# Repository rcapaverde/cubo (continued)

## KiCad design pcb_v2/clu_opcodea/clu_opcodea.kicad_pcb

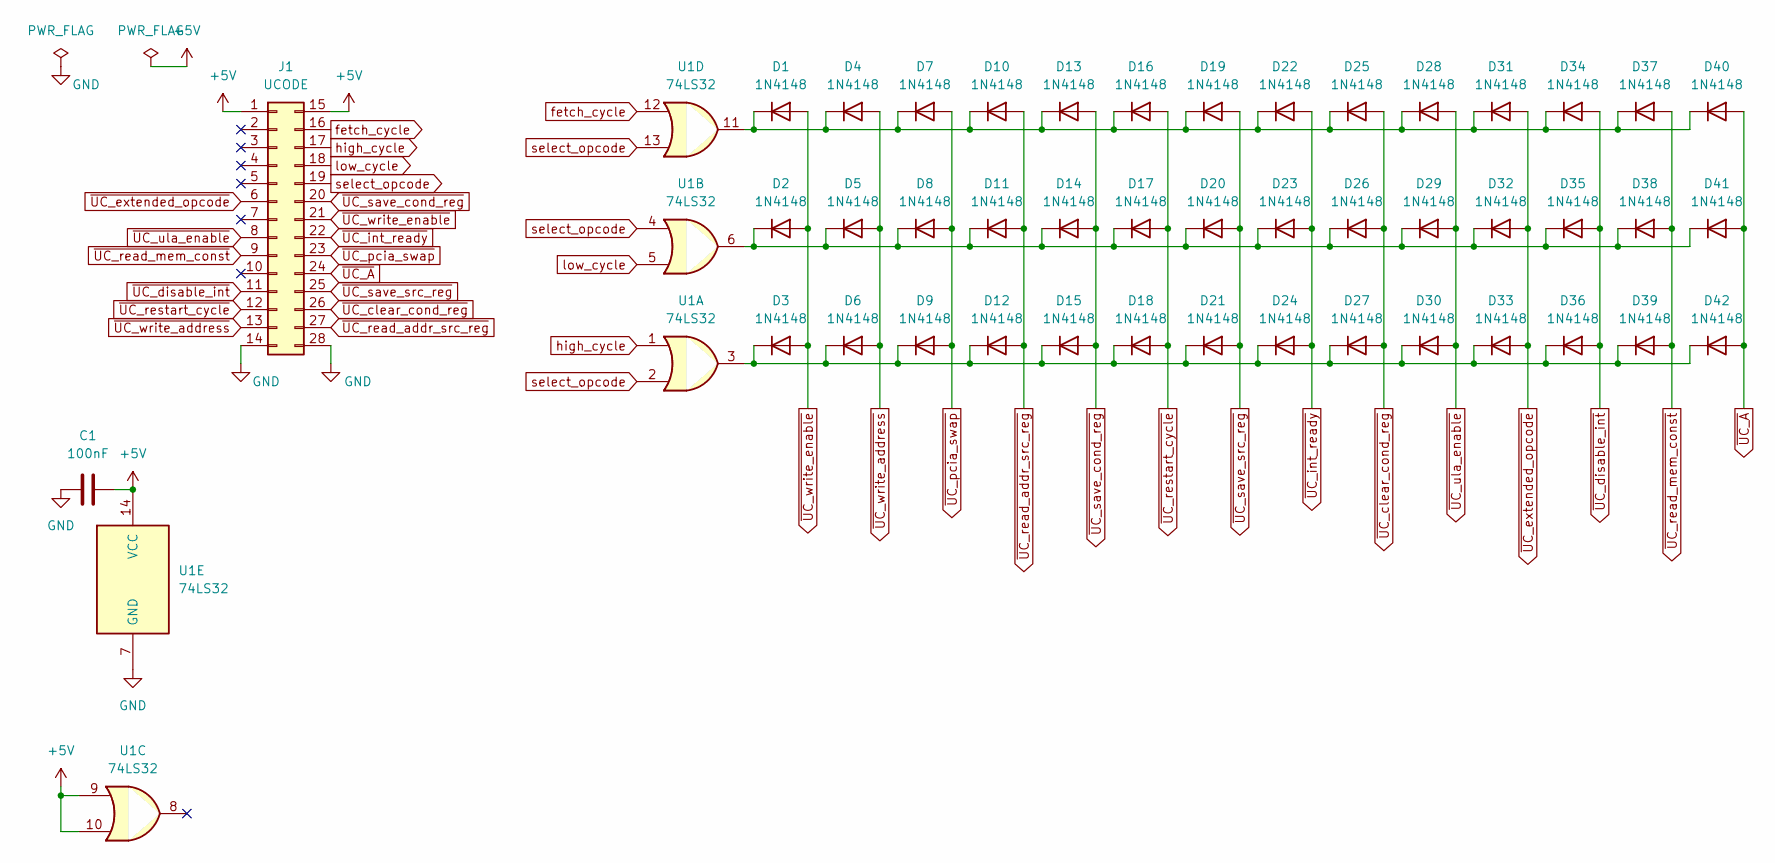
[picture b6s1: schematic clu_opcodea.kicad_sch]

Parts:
C1: 100nF; C_Disc_D5.1mm_W3.2mm_P5.00mm
D1, D2, D3, D4, D5, D6, D7, D8, D9, D10, D11, D12, D13, D14, D15, D16, D17, D18, D19, D20, D21, D22, D23, D24, D25, D26, D27, D28, D29, D30, D31, D32, D33, D34, D35, D36, D37, D38, D39, D40, D41, D42: 1N4148; D_DO-35_SOD27_P2.54mm_Vertical_AnodeUp
J1: UCODE; edge-conector-14
U1: 74LS32; DIP-14_W7.62mm

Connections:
+5V: C1.2, J1.1, J1.15, U1.9, U1.10, U1.14 (VCC)
GND: C1.1, J1.14, J1.28, U1.7 (GND)
unnamed: D1.1 (K), D4.1 (K), D7.1 (K), D10.1 (K), D13.1 (K), D16.1 (K), D19.1 (K), D22.1 (K), D25.1 (K), D28.1 (K), D31.1 (K), D34.1 (K), D37.1 (K), D40.1 (K), U1.11
unnamed: D2.1 (K), D5.1 (K), D8.1 (K), D11.1 (K), D14.1 (K), D17.1 (K), D20.1 (K), D23.1 (K), D26.1 (K), D29.1 (K), D32.1 (K), D35.1 (K), D38.1 (K), D41.1 (K), U1.6
unnamed: D3.1 (K), D6.1 (K), D9.1 (K), D12.1 (K), D15.1 (K), D18.1 (K), D21.1 (K), D24.1 (K), D27.1 (K), D30.1 (K), D33.1 (K), D36.1 (K), D39.1 (K), D42.1 (K), U1.3
fetch_cycle: J1.16, U1.12
high_cycle: J1.17, U1.1
low_cycle: J1.18, U1.5
select_opcode: J1.19, U1.2, U1.4, U1.13
~UC_A: D40.2 (A), D41.2 (A), D42.2 (A), J1.24
~UC_clear_cond_reg: D25.2 (A), D26.2 (A), D27.2 (A), J1.26
~UC_disable_int: D34.2 (A), D35.2 (A), D36.2 (A), J1.11
~UC_extended_opcode: D31.2 (A), D32.2 (A), D33.2 (A), J1.6
~UC_int_ready: D22.2 (A), D23.2 (A), D24.2 (A), J1.22
~UC_pcia_swap: D7.2 (A), D8.2 (A), D9.2 (A), J1.23
~UC_read_addr_src_reg: D10.2 (A), D11.2 (A), D12.2 (A), J1.27
~UC_read_mem_const: D37.2 (A), D38.2 (A), D39.2 (A), J1.9
~UC_restart_cycle: D16.2 (A), D17.2 (A), D18.2 (A), J1.12
~UC_save_cond_reg: D13.2 (A), D14.2 (A), D15.2 (A), J1.20
~UC_save_src_reg: D19.2 (A), D20.2 (A), D21.2 (A), J1.25
~UC_ula_enable: D28.2 (A), D29.2 (A), D30.2 (A), J1.8
~UC_write_address: D4.2 (A), D5.2 (A), D6.2 (A), J1.13
~UC_write_enable: D1.2 (A), D2.2 (A), D3.2 (A), J1.21

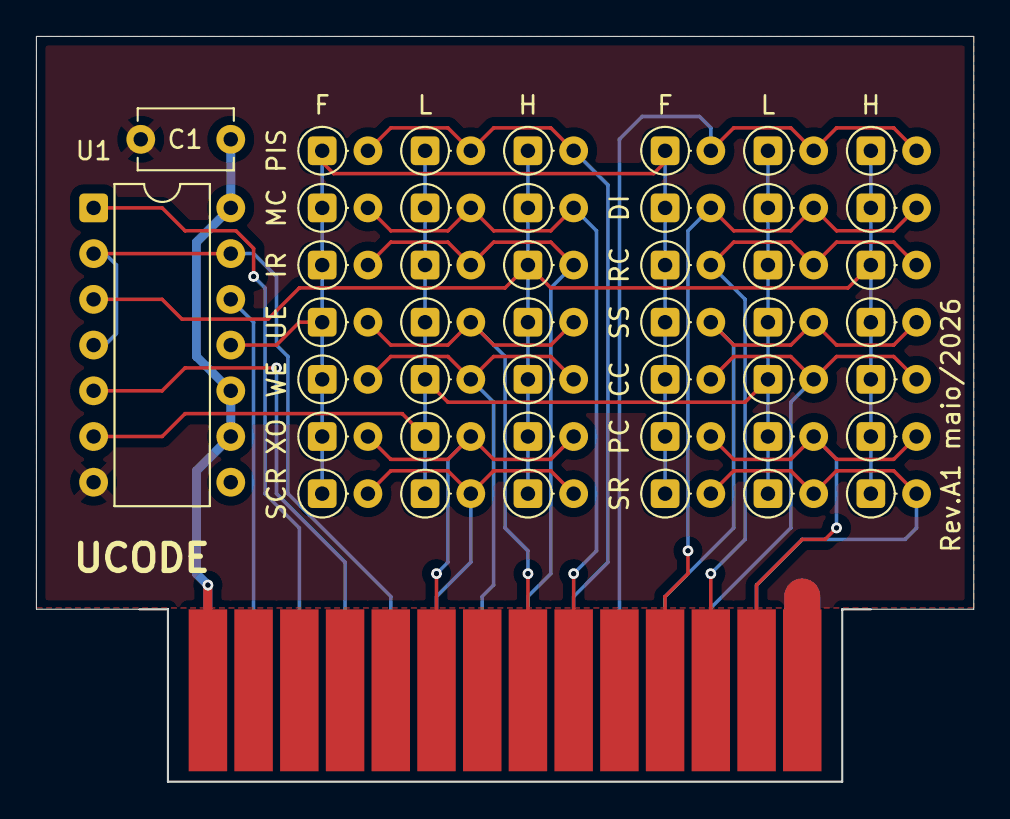
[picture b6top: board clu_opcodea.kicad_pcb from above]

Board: 2 copper layers, 52.1 x 41.4 mm, 45 parts (0 on the bottom side), 23 nets.

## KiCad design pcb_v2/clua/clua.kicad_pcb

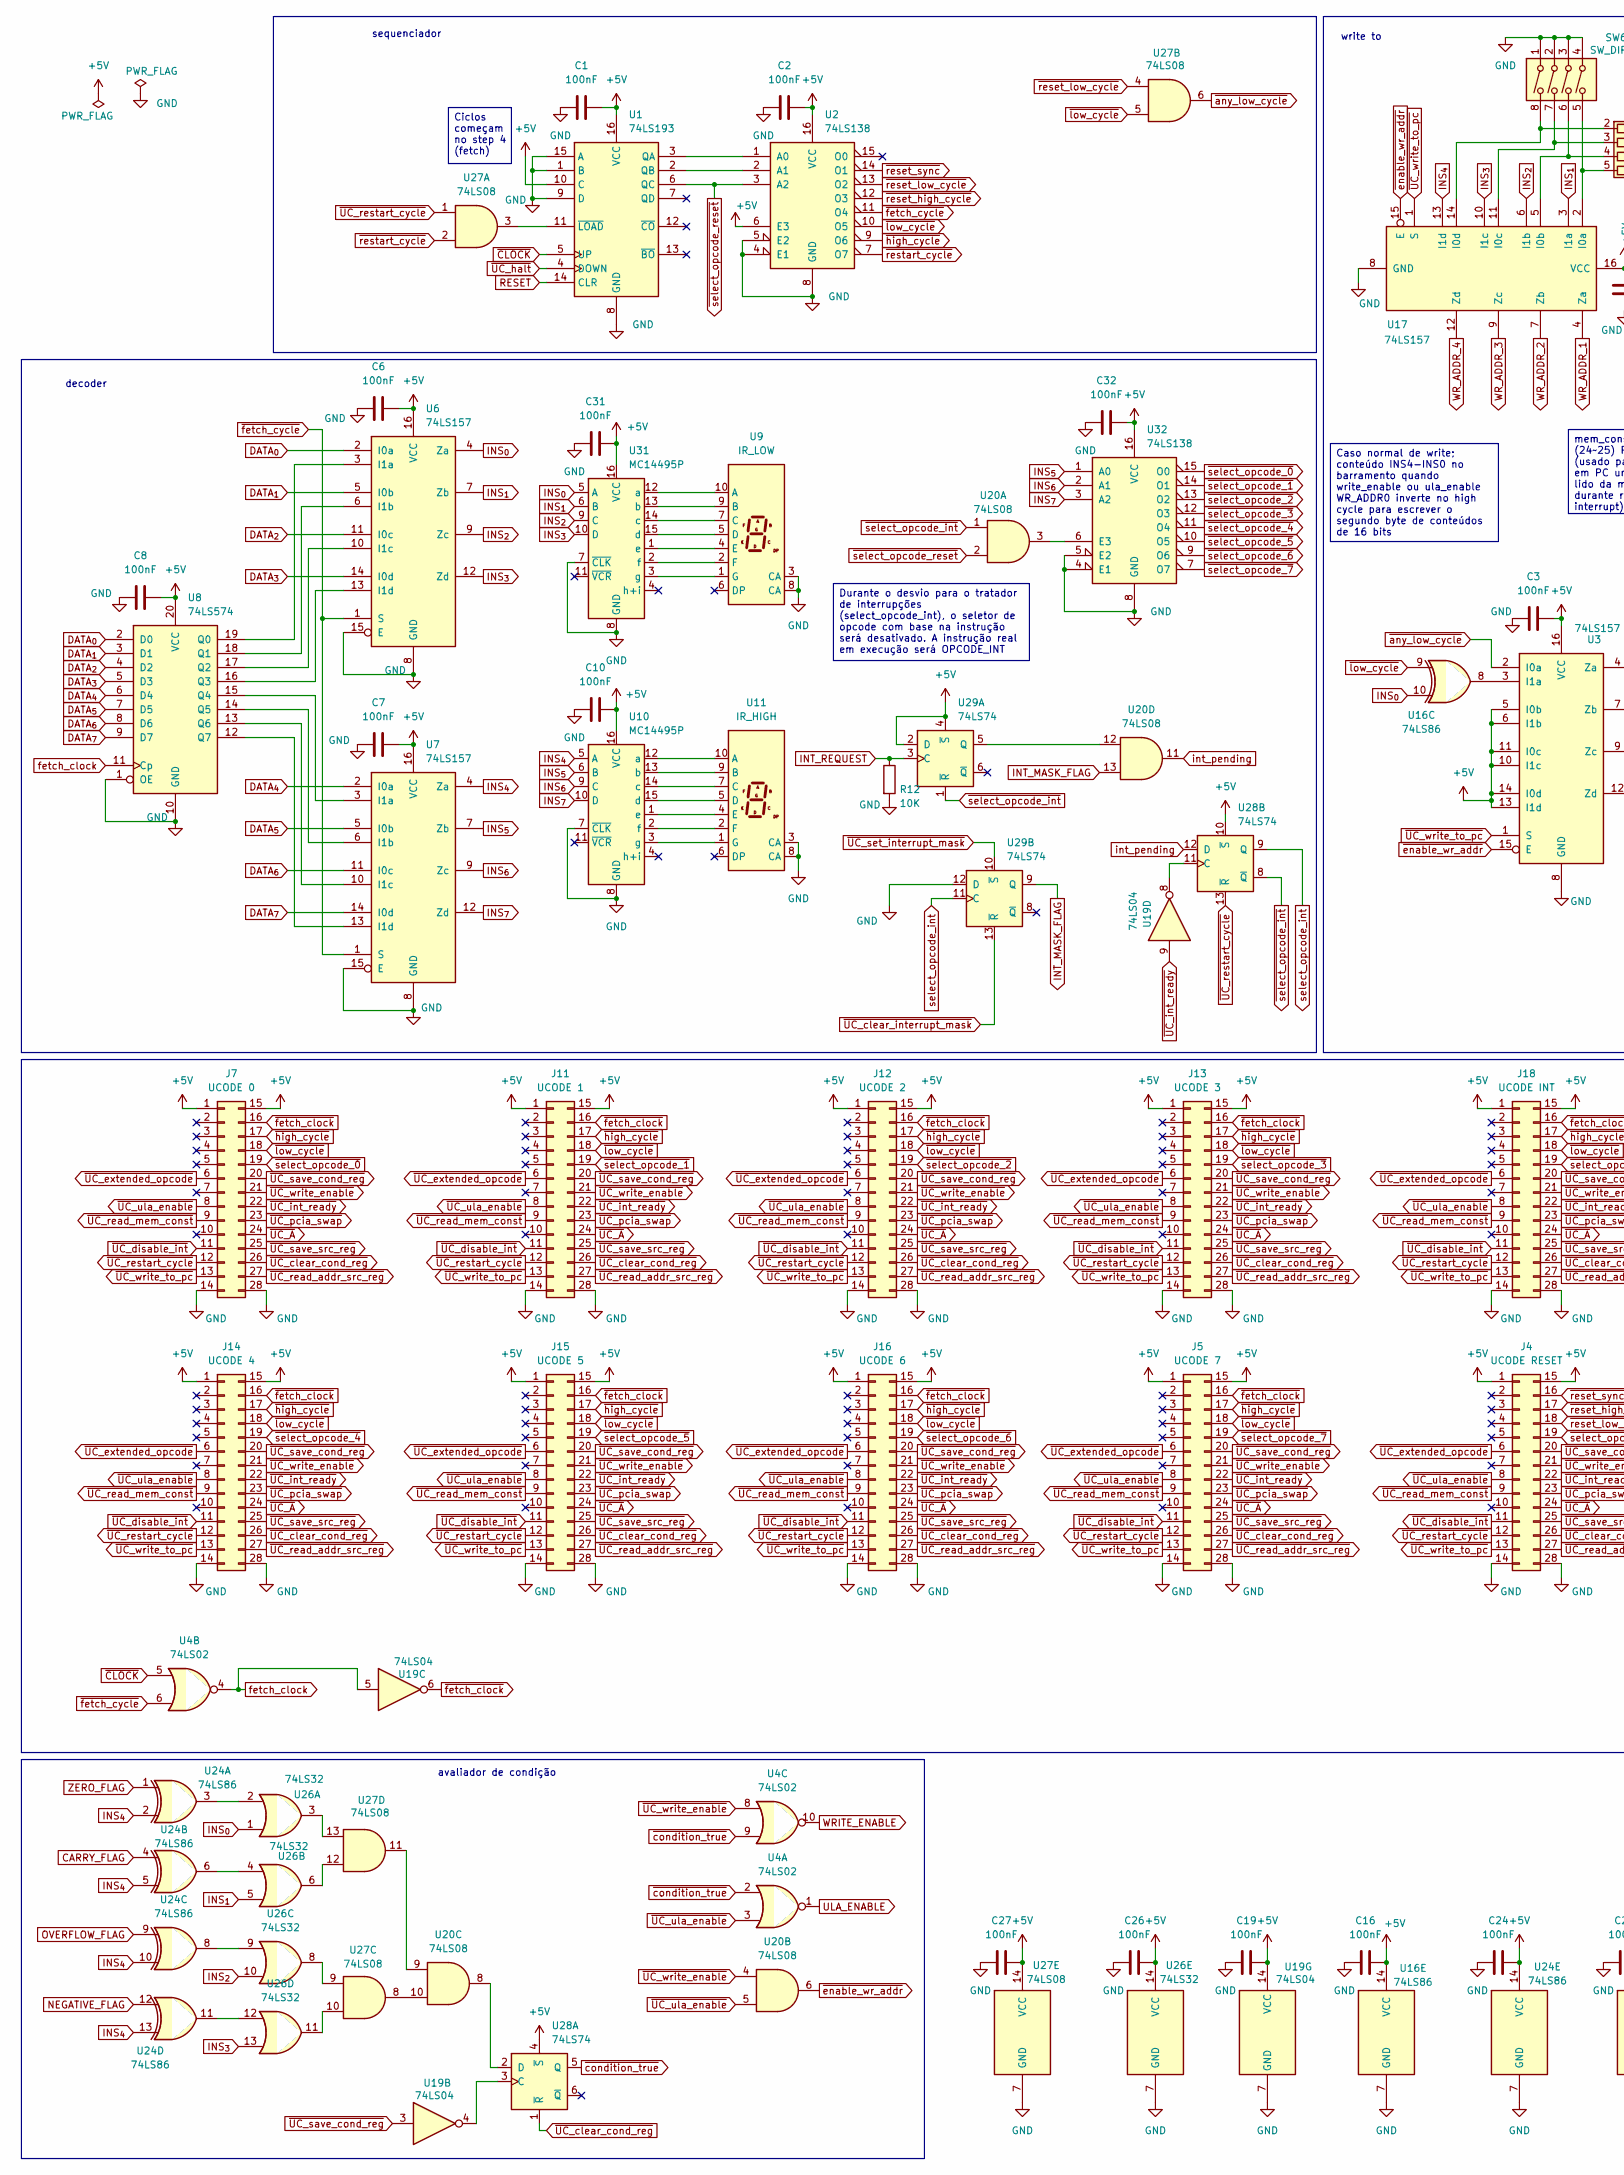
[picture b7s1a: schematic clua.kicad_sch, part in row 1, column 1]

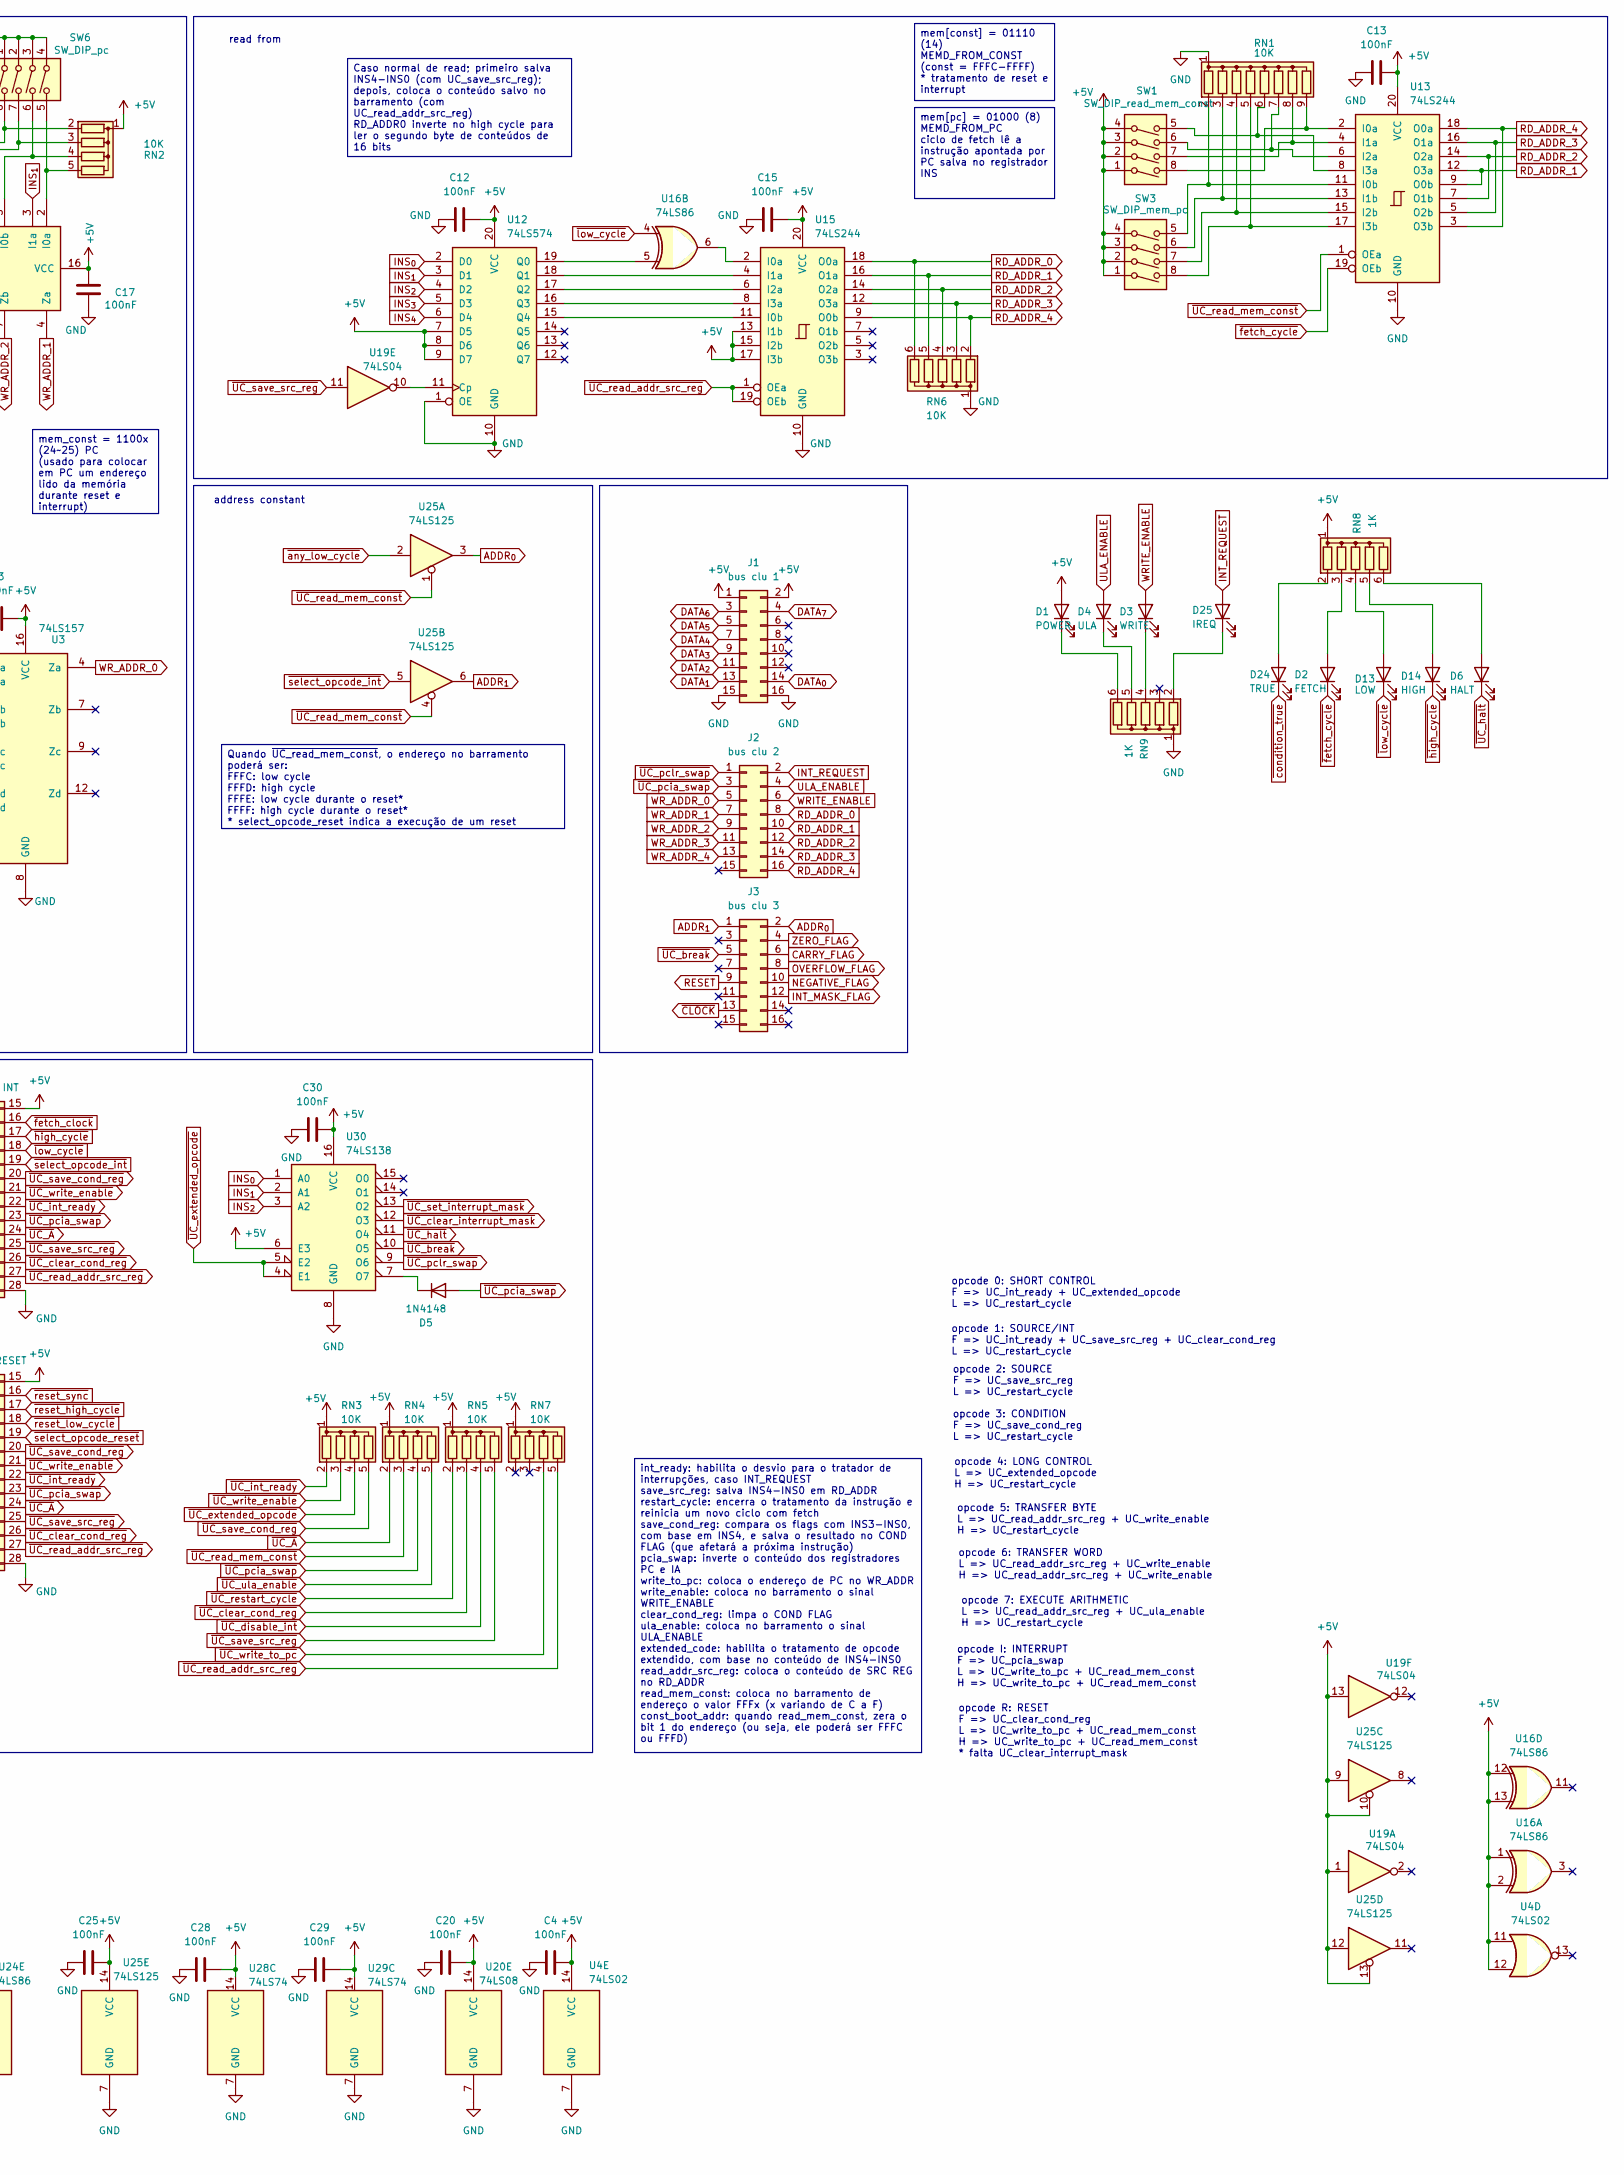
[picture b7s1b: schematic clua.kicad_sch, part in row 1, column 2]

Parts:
C1, C2, C3, C4, C6, C7, C8, C10, C12, C13, C15, C16, C17, C19, C20, C24, C25, C26, C27, C28, C29, C30, C31, C32: 100nF; C_Disc_D5.1mm_W3.2mm_P5.00mm
D1: POWER; LED_D5.0mm
D2: FETCH; LED_D5.0mm
D3: WRITE; LED_D5.0mm
D4: ULA; LED_D5.0mm
D5: 1N4148; D_DO-35_SOD27_P7.62mm_Horizontal
D6: HALT; LED_D5.0mm
D13: LOW; LED_D5.0mm
D14: HIGH; LED_D5.0mm
D24: TRUE; LED_D5.0mm
D25: IREQ; LED_D5.0mm
J1: bus clu 1; conector 02x08
J2: bus clu 2; conector 02x08
J3: bus clu 3; conector 02x08
J4: UCODE RESET; male-edge-connector-28
J5: UCODE 7; male-edge-connector-28
J7: UCODE 0; male-edge-connector-28
J11: UCODE 1; male-edge-connector-28
J12: UCODE 2; male-edge-connector-28
J13: UCODE 3; male-edge-connector-28
J14: UCODE 4; male-edge-connector-28
J15: UCODE 5; male-edge-connector-28
J16: UCODE 6; male-edge-connector-28
J18: UCODE INT; male-edge-connector-28
R12: 10K; R_Axial_DIN0207_L6.3mm_D2.5mm_P7.62mm_Horizontal
RN1: 10K; R_Array_SIP9
RN2, RN3, RN4, RN5, RN7: 10K; R_Array_SIP5
RN6: 10K; R_Array_SIP6
RN8, RN9: 1K; R_Array_SIP6
SW1: SW_DIP_read_mem_const; SW_DIP_SPSTx04_Slide_6.7x11.72mm_W7.62mm_P2.54mm_LowProfile
SW3: SW_DIP_mem_pc; SW_DIP_SPSTx04_Slide_6.7x11.72mm_W7.62mm_P2.54mm_LowProfile
SW6: SW_DIP_pc; SW_DIP_SPSTx04_Slide_6.7x11.72mm_W7.62mm_P2.54mm_LowProfile
U1: 74LS193; DIP-16_W7.62mm
U2, U30, U32: 74LS138; DIP-16_W7.62mm
U3, U6, U7, U17: 74LS157; DIP-16_W7.62mm
U4: 74LS02; DIP-14_W7.62mm
U8, U12: 74LS574; DIP-20_W7.62mm
U9: IR_LOW; Sx39-1xxxxx
U10, U31: MC14495P; DIP-16_W7.62mm
U11: IR_HIGH; Sx39-1xxxxx
U13, U15: 74LS244; DIP-20_W7.62mm
U16, U24: 74LS86; DIP-14_W7.62mm
U19: 74LS04; DIP-14_W7.62mm
U20, U27: 74LS08; DIP-14_W7.62mm
U25: 74LS125; DIP-14_W7.62mm
U26: 74LS32; DIP-14_W7.62mm
U28, U29: 74LS74; DIP-14_W7.62mm

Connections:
+5V: C1.2, C2.2, C3.2, C4.2, C6.2, C7.2, C8.2, C10.2, C12.2, C13.2, C15.2, C16.2, C17.2, C19.2, C20.2, C24.2, C25.2, C26.2, C27.2, C28.2, C29.2, C30.2, C31.2, C32.2, D1.2 (A), J1.1, J1.2, J4.1, J4.15, J5.1, J5.15, J7.1, J7.15, J11.1, J11.15, J12.1, J12.15, J13.1, J13.15, J14.1, J14.15, J15.1, J15.15, J16.1, J16.15, J18.1, J18.15, RN2.1 (common), RN3.1 (common), RN4.1 (common), RN5.1 (common), RN7.1 (common), RN8.1 (common), SW1.1, SW1.2, SW1.3, SW1.4, SW3.1, SW3.2, SW3.3, SW3.4, U1.10 (C), U1.16 (VCC), U2.6 (E3), U2.16 (VCC), U3.5 (I0b), U3.6 (I1b), U3.10 (I1c), U3.11 (I0c), U3.13 (I1d), U3.14 (I0d), U3.16 (VCC), U4.11, U4.12, U4.14 (VCC), U6.16 (VCC), U7.16 (VCC), U8.20 (VCC), U10.16 (VCC), U12.7 (D5), U12.8 (D6), U12.9 (D7), U12.20 (VCC), U13.20 (VCC), U15.13 (I1b), U15.15 (I2b), U15.17 (I3b), U15.20 (VCC), U16.1, U16.2, U16.12, U16.13, U16.14 (VCC), U17.16 (VCC), U19.1, U19.13, U19.14 (VCC), U20.14 (VCC), U24.14 (VCC), U25.9, U25.10, U25.12, U25.13, U25.14 (VCC), U26.14 (VCC), U27.14 (VCC), U28.4 (~S), U28.10 (~S), U28.14 (VCC), U29.2 (D), U29.4 (~S), U29.14 (VCC), U30.6 (E3), U30.16 (VCC), U31.16 (VCC), U32.16 (VCC)
ADDR_{0}: J3.2, U25.3
ADDR_{1}: J3.1, U25.6
CARRY_FLAG: J3.6, U24.4
DATA_{0}: J1.14, U6.2 (I0a), U8.2 (D0)
DATA_{1}: J1.13, U6.5 (I0b), U8.3 (D1)
DATA_{2}: J1.11, U6.11 (I0c), U8.4 (D2)
DATA_{3}: J1.9, U6.14 (I0d), U8.5 (D3)
DATA_{4}: J1.7, U7.2 (I0a), U8.6 (D4)
DATA_{5}: J1.5, U7.5 (I0b), U8.7 (D5)
DATA_{6}: J1.3, U7.11 (I0c), U8.8 (D6)
DATA_{7}: J1.4, U7.14 (I0d), U8.9 (D7)
GND: C1.1, C2.1, C3.1, C4.1, C6.1, C7.1, C8.1, C10.1, C12.1, C13.1, C15.1, C16.1, C17.1, C19.1, C20.1, C24.1, C25.1, C26.1, C27.1, C28.1, C29.1, C30.1, C31.1, C32.1, J1.15, J1.16, J4.14, J4.28, J5.14, J5.28, J7.14, J7.28, J11.14, J11.28, J12.14, J12.28, J13.14, J13.28, J14.14, J14.28, J15.14, J15.28, J16.14, J16.28, J18.14, J18.28, R12.2, RN1.1 (common), RN6.1 (common), RN9.1 (common), SW6.1, SW6.2, SW6.3, SW6.4, U1.1 (B), U1.8 (GND), U1.9 (D), U1.15 (A), U2.4 (E1), U2.5 (E2), U2.8 (GND), U3.8 (GND), U4.7 (GND), U6.8 (GND), U6.15 (E), U7.8 (GND), U7.15 (E), U8.1 (OE), U8.10 (GND), U9.3 (CA), U9.8 (CA), U10.7 (~CLK), U10.8 (GND), U11.3 (CA), U11.8 (CA), U12.1 (OE), U12.10 (GND), U13.10 (GND), U15.10 (GND), U16.7 (GND), U17.8 (GND), U19.7 (GND), U20.7 (GND), U24.7 (GND), U25.7 (GND), U26.7 (GND), U27.7 (GND), U28.7 (GND), U29.7 (GND), U29.12 (D), U30.8 (GND), U31.7 (~CLK), U31.8 (GND), U32.4 (E1), U32.5 (E2), U32.8 (GND)
INS_{0}: U6.4 (Za), U12.2 (D0), U16.10, U26.1, U30.1 (A0), U31.5 (A)
INS_{1}: U6.7 (Zb), U12.3 (D1), U17.3 (I1a), U26.5, U30.2 (A1), U31.6 (B)
INS_{2}: U6.9 (Zc), U12.4 (D2), U17.6 (I1b), U26.10, U30.3 (A2), U31.9 (C)
INS_{3}: U6.12 (Zd), U12.5 (D3), U17.10 (I1c), U26.13, U31.10 (D)
INS_{4}: U7.4 (Za), U10.5 (A), U12.6 (D4), U17.13 (I1d), U24.2, U24.5, U24.10, U24.13
INS_{5}: U7.7 (Zb), U10.6 (B), U32.1 (A0)
INS_{6}: U7.9 (Zc), U10.9 (C), U32.2 (A1)
INS_{7}: U7.12 (Zd), U10.10 (D), U32.3 (A2)
INT_MASK_FLAG: J3.12, U20.13, U29.9 (Q)
INT_REQUEST: D25.2 (A), J2.2, R12.1, U29.3 (C)
NEGATIVE_FLAG: J3.10, U24.12
unnamed: D1.1 (K), RN9.6 (R5)
unnamed: D2.2 (A), RN8.3 (R2)
unnamed: D3.1 (K), RN9.4 (R3)
unnamed: D4.1 (K), RN9.5 (R4)
unnamed: D5.1 (K), U30.7 (O7)
unnamed: D6.2 (A), RN8.6 (R5)
unnamed: D13.2 (A), RN8.4 (R3)
unnamed: D14.2 (A), RN8.5 (R4)
unnamed: D24.2 (A), RN8.2 (R1)
unnamed: D25.1 (K), RN9.2 (R1)
unnamed: RN1.2 (R1), SW3.5, U13.11 (I0b)
unnamed: RN1.3 (R2), SW3.6, U13.13 (I1b)
unnamed: RN1.4 (R3), SW3.7, U13.15 (I2b)
unnamed: RN1.5 (R4), SW3.8, U13.17 (I3b)
unnamed: RN1.6 (R5), SW1.5, U13.8 (I3a)
unnamed: RN1.7 (R6), SW1.6, U13.6 (I2a)
unnamed: RN1.8 (R7), SW1.7, U13.4 (I1a)
unnamed: RN1.9 (R8), SW1.8, U13.2 (I0a)
unnamed: RN2.2 (R1), SW6.8, U17.14 (I0d)
unnamed: RN2.3 (R2), SW6.7, U17.11 (I0c)
unnamed: RN2.4 (R3), SW6.6, U17.5 (I0b)
unnamed: RN2.5 (R4), SW6.5, U17.2 (I0a)
unnamed: U1.3 (QA), U2.1 (A0)
unnamed: U1.2 (QB), U2.2 (A1)
unnamed: U1.11 (~LOAD), U27.3
unnamed: U3.3 (I1a), U16.8
unnamed: U6.3 (I1a), U8.19 (Q0)
unnamed: U6.6 (I1b), U8.18 (Q1)
unnamed: U6.10 (I1c), U8.17 (Q2)
unnamed: U6.13 (I1d), U8.16 (Q3)
unnamed: U7.3 (I1a), U8.15 (Q4)
unnamed: U7.6 (I1b), U8.14 (Q5)
unnamed: U7.10 (I1c), U8.13 (Q6)
unnamed: U7.13 (I1d), U8.12 (Q7)
unnamed: U10.12 (a), U11.10 (A)
unnamed: U10.13 (b), U11.9 (B)
unnamed: U10.14 (c), U11.7 (C)
unnamed: U10.15 (d), U11.5 (D)
unnamed: U10.1 (e), U11.4 (E)
unnamed: U10.2 (f), U11.2 (F)
unnamed: U10.3 (g), U11.1 (G)
unnamed: U12.11 (Cp), U19.10
unnamed: U12.19 (Q0), U16.5
unnamed: U12.18 (Q1), U15.4 (I1a)
unnamed: U12.17 (Q2), U15.6 (I2a)
unnamed: U12.16 (Q3), U15.8 (I3a)
unnamed: U12.15 (Q4), U15.11 (I0b)
unnamed: U15.2 (I0a), U16.6
unnamed: U20.9, U27.11
unnamed: U20.10, U27.8
unnamed: U24.3, U26.2
unnamed: U24.6, U26.4
unnamed: U24.8, U26.9
unnamed: U24.11, U26.12
unnamed: U26.3, U27.13
unnamed: U26.6, U27.12
unnamed: U26.8, U27.9
unnamed: U26.11, U27.10
unnamed: U19.4, U28.3 (C)
unnamed: U20.8, U28.2 (D)
unnamed: U19.8, U28.11 (C)
unnamed: U20.12, U29.5 (Q)
unnamed: U9.10 (A), U31.12 (a)
unnamed: U9.9 (B), U31.13 (b)
unnamed: U9.7 (C), U31.14 (c)
unnamed: U9.5 (D), U31.15 (d)
unnamed: U9.4 (E), U31.1 (e)
unnamed: U9.2 (F), U31.2 (f)
unnamed: U9.1 (G), U31.3 (g)
unnamed: U20.3, U32.6 (E3)
OVERFLOW_FLAG: J3.8, U24.9
RD_ADDR_0: J2.8, RN6.6 (R5), U15.18 (O0a)
RD_ADDR_1: J2.10, RN6.5 (R4), U13.9 (O0b), U13.12 (O3a), U15.16 (O1a)
RD_ADDR_2: J2.12, RN6.4 (R3), U13.7 (O1b), U13.14 (O2a), U15.14 (O2a)
RD_ADDR_3: J2.14, RN6.3 (R2), U13.5 (O2b), U13.16 (O1a), U15.12 (O3a)
RD_ADDR_4: J2.16, RN6.2 (R1), U13.3 (O3b), U13.18 (O0a), U15.9 (O0b)
RESET: J3.9, U1.14 (CLR)
ULA_ENABLE: D4.2 (A), J2.4, U4.1
WRITE_ENABLE: D3.2 (A), J2.6, U4.10
WR_ADDR_0: J2.5, U3.4 (Za)
WR_ADDR_1: J2.7, U17.4 (Za)
WR_ADDR_2: J2.9, U17.7 (Zb)
WR_ADDR_3: J2.11, U17.9 (Zc)
WR_ADDR_4: J2.13, U17.12 (Zd)
ZERO_FLAG: J3.4, U24.1
fetch_clock: U4.4, U8.11 (Cp), U19.5
int_pending: U20.11, U28.12 (D)
select_opcode_int: U28.9 (Q), U29.11 (C)
~CLOCK: J3.13, U1.5 (UP), U4.5
~UC_A: J4.24, J5.24, J7.24, J11.24, J12.24, J13.24, J14.24, J15.24, J16.24, J18.24, RN4.2 (R1)
~UC_break: J3.5, U30.10 (O5)
~UC_clear_cond_reg: J4.26, J5.26, J7.26, J11.26, J12.26, J13.26, J14.26, J15.26, J16.26, J18.26, RN5.3 (R2), U28.1 (~R)
~UC_clear_interrupt_mask: U29.13 (~R), U30.12 (O3)
~UC_disable_int: J4.11, J5.11, J7.11, J11.11, J12.11, J13.11, J14.11, J15.11, J16.11, J18.11, RN5.4 (R3)
~UC_extended_opcode: J4.6, J5.6, J7.6, J11.6, J12.6, J13.6, J14.6, J15.6, J16.6, J18.6, RN3.4 (R3), U30.4 (E1), U30.5 (E2)
~UC_halt: D6.1 (K), U1.4 (DOWN), U30.11 (O4)
~UC_int_ready: J4.22, J5.22, J7.22, J11.22, J12.22, J13.22, J14.22, J15.22, J16.22, J18.22, RN3.2 (R1), U19.9
~UC_pcia_swap: D5.2 (A), J2.3, J4.23, J5.23, J7.23, J11.23, J12.23, J13.23, J14.23, J15.23, J16.23, J18.23, RN4.4 (R3)
~UC_pclr_swap: J2.1, U30.9 (O6)
~UC_read_addr_src_reg: J4.27, J5.27, J7.27, J11.27, J12.27, J13.27, J14.27, J15.27, J16.27, J18.27, RN7.5 (R4), U15.1 (OEa), U15.19 (OEb)
~UC_read_mem_const: J4.9, J5.9, J7.9, J11.9, J12.9, J13.9, J14.9, J15.9, J16.9, J18.9, RN4.3 (R2), U13.1 (OEa), U25.1, U25.4
~UC_restart_cycle: J4.12, J5.12, J7.12, J11.12, J12.12, J13.12, J14.12, J15.12, J16.12, J18.12, RN5.2 (R1), U27.1, U28.13 (~R)
~UC_save_cond_reg: J4.20, J5.20, J7.20, J11.20, J12.20, J13.20, J14.20, J15.20, J16.20, J18.20, RN3.5 (R4), U19.3
~UC_save_src_reg: J4.25, J5.25, J7.25, J11.25, J12.25, J13.25, J14.25, J15.25, J16.25, J18.25, RN5.5 (R4), U19.11
~UC_set_interrupt_mask: U29.10 (~S), U30.13 (O2)
~UC_ula_enable: J4.8, J5.8, J7.8, J11.8, J12.8, J13.8, J14.8, J15.8, J16.8, J18.8, RN4.5 (R4), U4.3, U20.5
~UC_write_enable: J4.21, J5.21, J7.21, J11.21, J12.21, J13.21, J14.21, J15.21, J16.21, J18.21, RN3.3 (R2), U4.8, U20.4
~UC_write_to_pc: J4.13, J5.13, J7.13, J11.13, J12.13, J13.13, J14.13, J15.13, J16.13, J18.13, RN7.4 (R3), U3.1 (S), U17.1 (S)
~any_low_cycle: U3.2 (I0a), U25.2, U27.6
~condition_true: D24.1 (K), U4.2, U4.9, U28.5 (Q)
~enable_wr_addr: U3.15 (E), U17.15 (E), U20.6
~fetch_clock: J5.16, J7.16, J11.16, J12.16, J13.16, J14.16, J15.16, J16.16, J18.16, U19.6
~fetch_cycle: D2.1 (K), U2.11 (O4), U4.6, U6.1 (S), U7.1 (S), U13.19 (OEb)
~high_cycle: D14.1 (K), J5.17, J7.17, J11.17, J12.17, J13.17, J14.17, J15.17, J16.17, J18.17, U2.9 (O6)
~low_cycle: D13.1 (K), J5.18, J7.18, J11.18, J12.18, J13.18, J14.18, J15.18, J16.18, J18.18, U2.10 (O5), U16.4, U16.9, U27.5
~reset_high_cycle: J4.17, U2.12 (O3)
~reset_low_cycle: J4.18, U2.13 (O2), U27.4
~reset_sync: J4.16, U2.14 (O1)
~restart_cycle: U2.7 (O7), U27.2
~select_opcode_0: J7.19, U32.15 (O0)
~select_opcode_1: J11.19, U32.14 (O1)
~select_opcode_2: J12.19, U32.13 (O2)
~select_opcode_3: J13.19, U32.12 (O3)
~select_opcode_4: J14.19, U32.11 (O4)
~select_opcode_5: J15.19, U32.10 (O5)
~select_opcode_6: J16.19, U32.9 (O6)
~select_opcode_7: J5.19, U32.7 (O7)
~select_opcode_int: J18.19, U20.1, U25.5, U28.8 (~Q), U29.1 (~R)
~select_opcode_reset: J4.19, U1.6 (QC), U2.3 (A2), U20.2

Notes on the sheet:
opcode 1: SOURCE/INT F => UC_int_ready + UC_save_src_reg + UC_clear_cond_reg L => UC_restart_cycle
opcode 2: SOURCE F => UC_save_src_reg L => UC_restart_cycle
sequenciador
write to
opcode 7: EXECUTE ARITHMETIC L => UC_read_addr_src_reg + UC_ula_enable H => UC_restart_cycle
avaliador de condição
decoder
read from
opcode 6: TRANSFER WORD L => UC_read_addr_src_reg + UC_write_enable H => UC_read_addr_src_reg + UC_write_enable
address constant
opcode R: RESET F => UC_clear_cond_reg L => UC_write_to_pc + UC_read_mem_const H => UC_write_to_pc + UC_read_mem_const * falta UC_clear_interrupt_mask
opcode 4: LONG CONTROL L => UC_extended_opcode H => UC_restart_cycle
opcode I: INTERRUPT F => UC_pcia_swap L => UC_write_to_pc + UC_read_mem_const H => UC_write_to_pc + UC_read_mem_const
opcode 3: CONDITION F => UC_save_cond_reg L => UC_restart_cycle
opcode 0: SHORT CONTROL F => UC_int_ready + UC_extended_opcode L => UC_restart_cycle
opcode 5: TRANSFER BYTE L => UC_read_addr_src_reg + UC_write_enable H => UC_restart_cycle
Caso normal de read; primeiro salva INS4-INS0 (com UC_save_src_reg); depois, coloca o conteúdo salvo no barramento (com UC_read_addr_src_reg) RD_ADDR0 inverte no high cycle para ler o segundo byte de conteúdos de 16 bits
mem_const = 1100x (24~25) PC (usado para colocar em PC um endereço lido da memória durante reset e interrupt)
Caso normal de write; conteúdo INS4-INS0 no barramento quando write_enable ou ula_enable WR_ADDR0 inverte no high cycle para escrever o segundo byte de conteúdos de 16 bits
Quando ~{UC_read_mem_const}, o endereço no barramento poderá ser: FFFC: low cycle FFFD: high cycle FFFE: low cycle durante o reset* FFFF: high cycle durante o reset* * select_opcode_reset indica a execução de um reset
Durante o desvio para o tratador de interrupções (select_opcode_int), o seletor de opcode com base na instrução será desativado. A instrução real em execução será OPCODE_INT
int_ready: habilita o desvio para o tratador de interrupções, caso INT_REQUEST save_src_reg: salva INS4-INS0 em RD_ADDR restart_cycle: encerra o tratamento da instrução e reinicia um novo ciclo com fetch save_cond_reg: compara os flags com INS3-INS0, com base em INS4, e salva o resultado no COND FL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
mem[pc] = 01000 (8) MEMD_FROM_PC ciclo de fetch lê a instrução apontada por PC salva no registrador INS
Ciclos começam no step 4 (fetch)
mem[const] = 01110 (14) MEMD_FROM_CONST (const = FFFC-FFFF) * tratamento de reset e interrupt

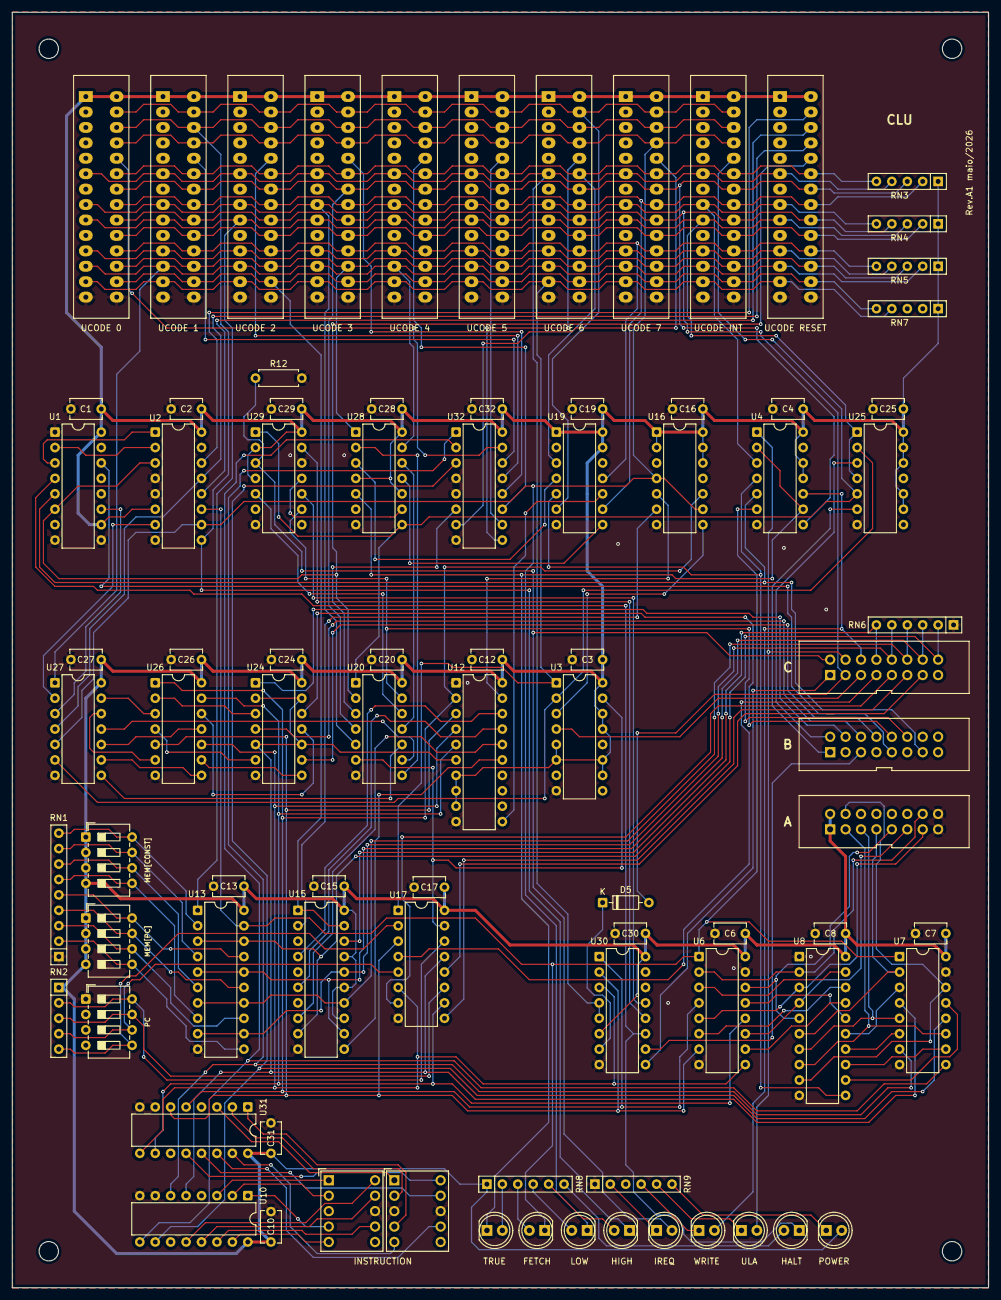
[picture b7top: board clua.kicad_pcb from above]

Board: 2 copper layers, 160.7 x 210.0 mm, 86 parts (0 on the bottom side), 153 nets.
